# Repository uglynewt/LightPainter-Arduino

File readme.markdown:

README
=======

Requirements
--------------

Install the [Adafruit NeoPixel] (https://github.com/adafruit/Adafruit_NeoPixel.git) into your Arduino environment to get this code to work.

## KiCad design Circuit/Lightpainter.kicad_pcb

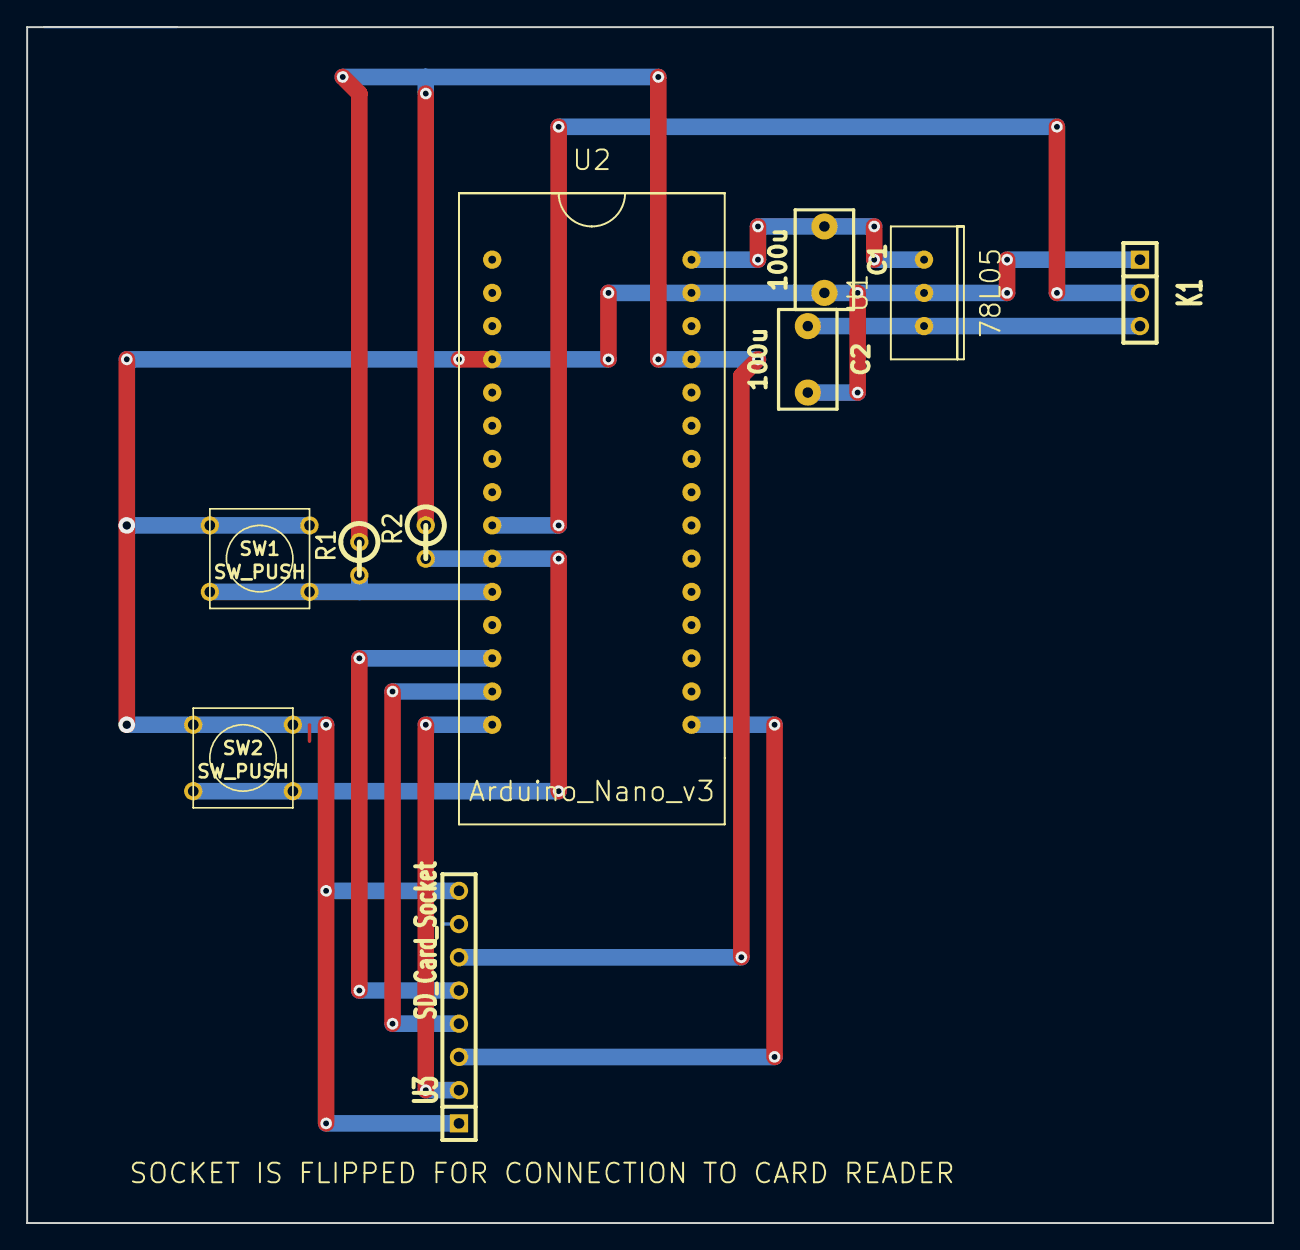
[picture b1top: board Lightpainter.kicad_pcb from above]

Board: 2 copper layers, 95.2 x 91.4 mm, 10 parts (0 on the bottom side), 11 nets.

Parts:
C1, C2: 100u; cnp_7x4.5mm
K1: CONN_3; SIL-3
R1, R2: 470k; R1
SW1, SW2: SW_PUSH; SW_PUSH_SMALL
U1: 78L05; 78L05-TO220-VERT
U2: Arduino_Nano_v3; ArduinoNano
U3: SD_Card_Socket; SIL-8

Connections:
+5V: R1.1, R2.1, U2.27, U3.3
+5VD: C2.1, K1.3, U1.3
GND: C1.2, C2.2, K1.1, SW1.1, SW2.1, U1.1, U2.4, U2.29, U3.1, U3.8
unnamed: R1.2, SW1.2, U2.11
unnamed: R2.2, SW2.2, U2.10
unnamed: U2.13, U3.4
unnamed: U2.14, U3.5
unnamed: U2.15, U3.7
unnamed: U2.16, U3.6
STRIP_DATA: K1.2, U2.9
VDD: C1.1, U1.2, U2.30

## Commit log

2014-05-15 Initial commit Light Painter
    Read images from an SD card and use them to draw images in space for
    long exposure photos.
2014-05-15 Added Readme
2014-09-01 Create folder to keep Arduino IDE happy
    Moved the .ino into its own folder with a name. This happened
    automatically.
2014-09-01 Horrid, lazy hacking to change filenames to nums
    I am almost embarrassed, but it was quicker than using sprintf (since
    that means pain since it’s not in Arduino)…
2014-09-01 Bugfix
    to make sure that the first image can be used
2015-04-07 Add schematic for board
    Board schematic for Light Painting workshop.
2015-04-08 Change pin connections to match the Arduino code
2015-04-08 Rats nest created
    something has messed up the schematic, and the 7805 isn’t connected
    properly. Rather than mess around to try to figure out the cause, edit
    the .net file manually
2015-04-08 PCB Layout started
2015-04-13 Added 'PCB'
    which is actually a layout idea for using veroboard
2015-04-16 Delete reference to Serial.h
    Apparently this header doesn’t exist, but you only get a warning (which
    is normally suppressed), and not an error.
2015-04-18 Fixed build error on Windows
    Seems like the SPI.h library is required to make this code build on
    Windows versions of the Arduino environment.
2015-04-29 Define pins for lightstrip and SD at top, use consistently throughout.
2015-04-29 Oops, use the right pin name.
2015-04-29 Use array of strings instead of switch statement.
